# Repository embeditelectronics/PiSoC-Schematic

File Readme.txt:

PiSoC Schematic
----------------

Includes Eagle schematic and board layout for the PiSoC.

Copyright (c) 2015, Embedit Electronics

This work is licensed under a Creative Commons Attribution-ShareAlike 3.0 License. You can view a copy of it here: http://creativecommons.org/licenses/by-sa/3.0/us/

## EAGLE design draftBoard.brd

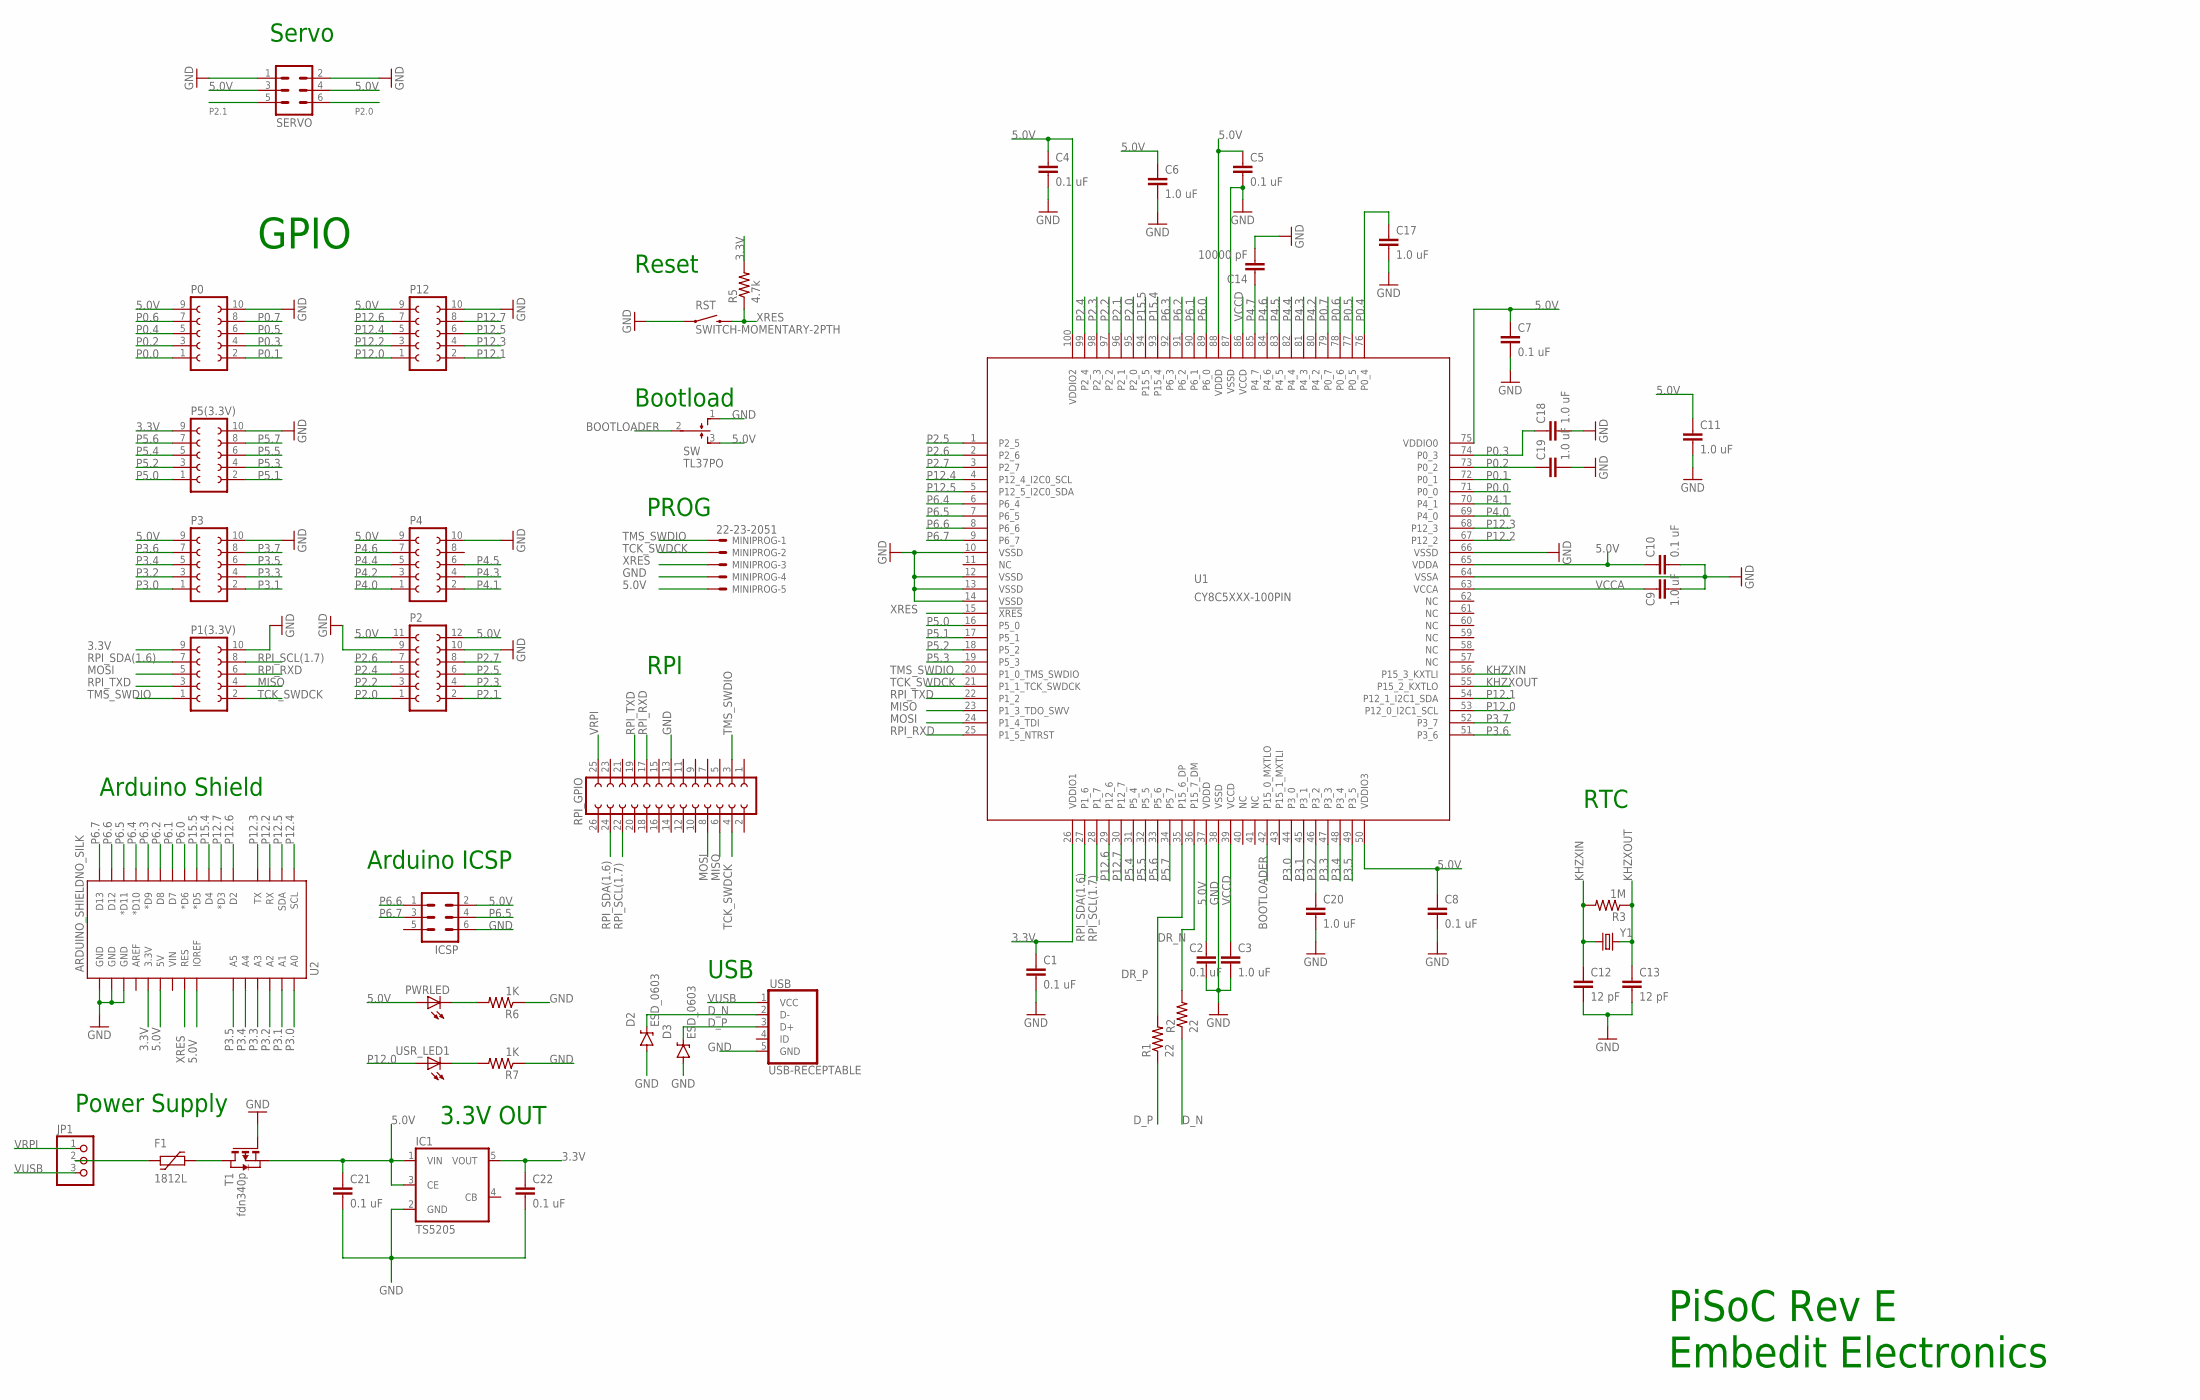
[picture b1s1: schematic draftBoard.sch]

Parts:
C1, C2, C4, C5, C7, C8, C10, C21, C22: 0.1 uF; 0603-CAP@1
C3, C6, C9, C11, C17, C18, C19, C20: 1.0 uF; 0603-CAP@1
C12, C13: 12 pF; 0603-CAP@1
C14: 10000 pF; 0603-CAP@1
D2, D3: ESD_0603; 0603-CAP
F1: 1812L
IC1: TS5205; SOT25
ICSP: MA03-2
JP1: PINHD-1X3; 1X03
MINIPROG: 22-23-2051
P0, P1(3.3V), P3, P4, P5(3.3V), P12: FE05-2
P2: FE06-2
PWRLED: LED0603; LED-0603
R1, R2: 22; 0603-RES
R3: 1M; 0603-RES
R5: 4.7k; 0603-RES
R6, R7: 1K; 0603-RES
RPI_GPIO: FE13-2
RST: SWITCH-MOMENTARY-2PTH; TACTILE-PTH
SERVO: MA03-2
SW: TL37PO; TL3XPO
T1: fdn340p; SOT-23
U1: CY8C5XXX-100PIN; TQFP-14X14-100
U2: ARDUINO_SHIELDNO_SILK; DUEMILANOVE_VIAS
USB: USB-RECEPTABLE; FCI-10103594-0001LF
USR_LED1: LED0603; LED-0603
Y1: CRYSTALTC26H; TC26H

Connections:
3.3V: C1.1, C22.1, IC1.5 (VOUT), P1(3.3V).9, P5(3.3V).9, R5.2, U1.26 (VDDIO1), U2.3.3V
5.0V: C2.1, C4.1, C5.1, C6.1, C7.1, C8.1, C10.1, C11.1, C21.1, IC1.1 (VIN), IC1.3 (CE), ICSP.2, MINIPROG.5, P0.9, P2.11, P2.12, P3.9, P4.9, P12.9, PWRLED.A, SERVO.3, SERVO.4, SW.3 (S), T1.2 (S), U1.37 (VDDD), U1.50 (VDDIO3), U1.65 (VDDA), U1.75 (VDDIO0), U1.88 (VDDD), U1.100 (VDDIO2), U2.5V, U2.IOREF
BOOTLOADER: SW.2, U1.42 (P15_0_MXTLO)
DR_N: R2.2, U1.36 (P15_7_DM)
DR_P: R1.2, U1.35 (P15_6_DP)
D_N: D2.1 (C), R2.1, USB.2 (D-)
D_P: D3.1 (C), R1.1, USB.3 (D+)
GND: C1.2, C2.2, C3.2, C4.2, C5.2, C6.2, C7.2, C8.2, C9.2, C10.2, C11.2, C12.2, C13.2, C14.2, C17.2, C18.2, C19.2, C20.2, C21.2, C22.2, D2.2 (A), D3.2 (A), IC1.2 (GND), ICSP.6, MINIPROG.4, P0.10, P1(3.3V).10, P2.9, P2.10, P3.10, P4.10, P5(3.3V).10, P12.10, R6.1, R7.1, RPI_GPIO.13, RST.1, SERVO.1, SERVO.2, SW.1 (O), T1.3 (G), U1.10 (VSSD), U1.12 (VSSD), U1.13 (VSSD), U1.14 (VSSD), U1.38 (VSSD), U1.64 (VSSA), U1.66 (VSSD), U1.87 (VSSD), U2.GND@0 (GND), U2.GND@1 (GND), U2.GND@2 (GND), USB.5 (GND)
KHZXIN: C12.1, R3.2, U1.56 (P15_3_KXTLI), Y1.1
KHZXOUT: C13.1, R3.1, U1.55 (P15_2_KXTLO), Y1.2
MISO: P1(3.3V).4, RPI_GPIO.6, U1.23 (P1_3_TDO_SWV)
MOSI: P1(3.3V).5, RPI_GPIO.8, U1.24 (P1_4_TDI)
unnamed: PWRLED.C, R6.2
unnamed: F1.P$1 (1), JP1.2
unnamed: F1.P$2 (2), T1.1 (D)
unnamed: R7.2, USR_LED1.C
P0.0: P0.1, U1.71 (P0_0)
P0.1: P0.2, U1.72 (P0_1)
P0.2: C19.1, P0.3, U1.73 (P0_2)
P0.3: C18.1, P0.4, U1.74 (P0_3)
P0.4: C17.1, P0.5, U1.76 (P0_4)
P0.5: P0.6, U1.77 (P0_5)
P0.6: P0.7, U1.78 (P0_6)
P0.7: P0.8, U1.79 (P0_7)
P2.0: P2.1, SERVO.6, U1.95 (P2_0)
P2.1: P2.2, SERVO.5, U1.96 (P2_1)
P2.2: P2.3, U1.97 (P2_2)
P2.3: P2.4, U1.98 (P2_3)
P2.4: P2.5, U1.99 (P2_4)
P2.5: P2.6, U1.1 (P2_5)
P2.6: P2.7, U1.2 (P2_6)
P2.7: P2.8, U1.3 (P2_7)
P3.0: P3.1, U1.44 (P3_0), U2.A0
P3.1: P3.2, U1.45 (P3_1), U2.A1
P3.2: C20.1, P3.3, U1.46 (P3_2), U2.A2
P3.3: P3.4, U1.47 (P3_3), U2.A3
P3.4: P3.5, U1.48 (P3_4), U2.A4
P3.5: P3.6, U1.49 (P3_5), U2.A5
P3.6: P3.7, U1.51 (P3_6)
P3.7: P3.8, U1.52 (P3_7)
P4.0: P4.1, U1.69 (P4_0)
P4.1: P4.2, U1.70 (P4_1)
P4.2: P4.3, U1.80 (P4_2)
P4.3: P4.4, U1.81 (P4_3)
P4.4: P4.5, U1.82 (P4_4)
P4.5: P4.6, U1.83 (P4_5)
P4.6: P4.7, U1.84 (P4_6)
P4.7: C14.1, U1.85 (P4_7)
P5.0: P5(3.3V).1, U1.16 (P5_0)
P5.1: P5(3.3V).2, U1.17 (P5_1)
P5.2: P5(3.3V).3, U1.18 (P5_2)
P5.3: P5(3.3V).4, U1.19 (P5_3)
P5.4: P5(3.3V).5, U1.31 (P5_4)
P5.5: P5(3.3V).6, U1.32 (P5_5)
P5.6: P5(3.3V).7, U1.33 (P5_6)
P5.7: P5(3.3V).8, U1.34 (P5_7)
P6.0: U1.89 (P6_0), U2.D6 (*D6)
P6.1: U1.90 (P6_1), U2.D7
P6.2: U1.91 (P6_2), U2.D8
P6.3: U1.92 (P6_3), U2.D9 (*D9)
P6.4: U1.6 (P6_4), U2.D10 (*D10)
P6.5: ICSP.4, U1.7 (P6_5), U2.D11 (*D11)
P6.6: ICSP.1, U1.8 (P6_6), U2.D12
P6.7: ICSP.3, U1.9 (P6_7), U2.D13
P12.0: P12.1, U1.53 (P12_0_I2C1_SCL), USR_LED1.A
P12.1: P12.2, U1.54 (P12_1_I2C1_SDA)
P12.2: P12.3, U1.67 (P12_2), U2.RX
P12.3: P12.4, U1.68 (P12_3), U2.TX
P12.4: P12.5, U1.4 (P12_4_I2C0_SCL), U2.SCL
P12.5: P12.6, U1.5 (P12_5_I2C0_SDA), U2.SDA
P12.6: P12.7, U1.29 (P12_6), U2.D2
P12.7: P12.8, U1.30 (P12_7), U2.D3 (*D3)
P15.4: U1.93 (P15_4), U2.D4
P15.5: U1.94 (P15_5), U2.D5 (*D5)
RPI_RXD: P1(3.3V).6, RPI_GPIO.17, U1.25 (P1_5_NTRST)
RPI_SCL(1.7): P1(3.3V).8, RPI_GPIO.22, U1.28 (P1_7)
RPI_SDA(1.6): P1(3.3V).7, RPI_GPIO.24, U1.27 (P1_6)
RPI_TXD: P1(3.3V).3, RPI_GPIO.19, U1.22 (P1_2)
TCK_SWDCK: MINIPROG.2, P1(3.3V).2, RPI_GPIO.4, U1.21 (P1_1_TCK_SWDCK)
TMS_SWDIO: MINIPROG.1, P1(3.3V).1, RPI_GPIO.3, U1.20 (P1_0_TMS_SWDIO)
VCCA: C9.1, U1.63 (VCCA)
VCCD: C3.1, U1.39 (VCCD), U1.86 (VCCD)
VRPI: JP1.1, RPI_GPIO.25
VUSB: JP1.3, USB.1 (VCC)
XRES: MINIPROG.3, R5.1, RST.3 (2), U1.15 (!XRES!), U2.RES

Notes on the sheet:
PiSoC Rev E Embedit Electronics
GPIO
PROG
Bootload
Reset
3.3V OUT
RTC
RPI
Arduino Shield
Arduino ICSP
Servo
USB
Power Supply

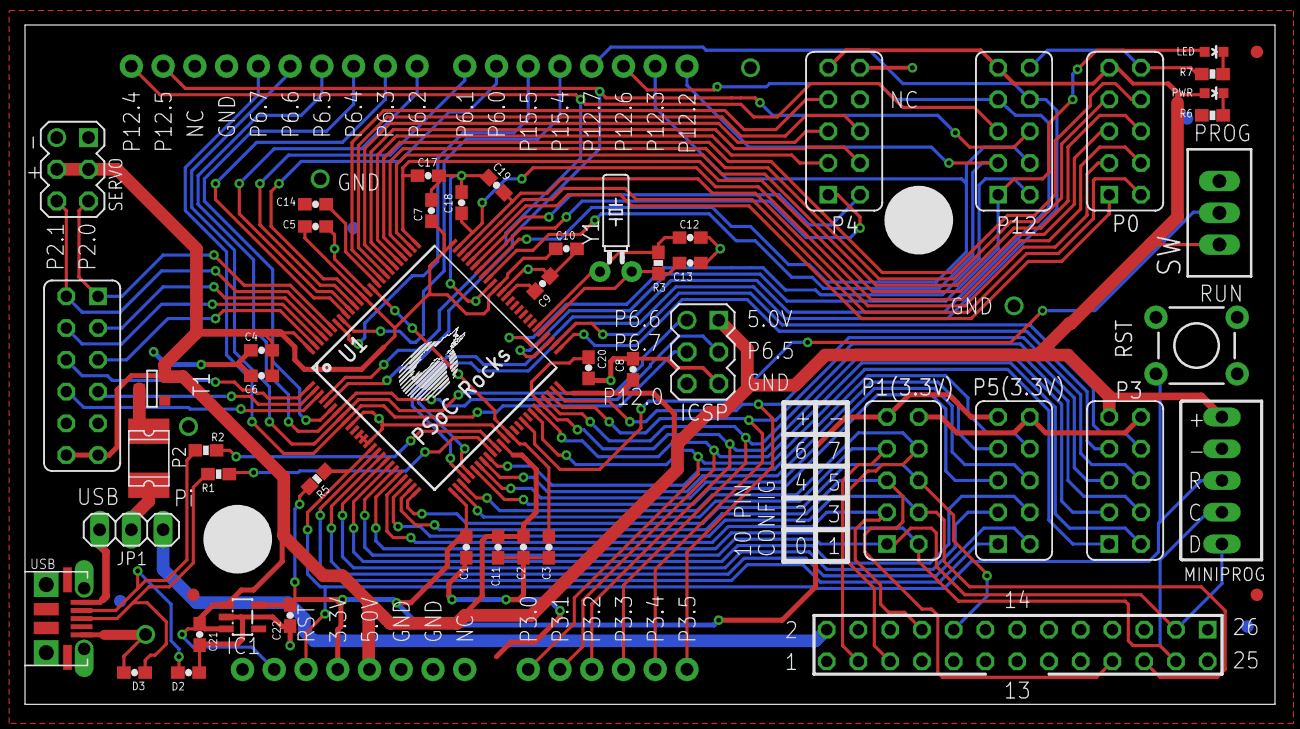
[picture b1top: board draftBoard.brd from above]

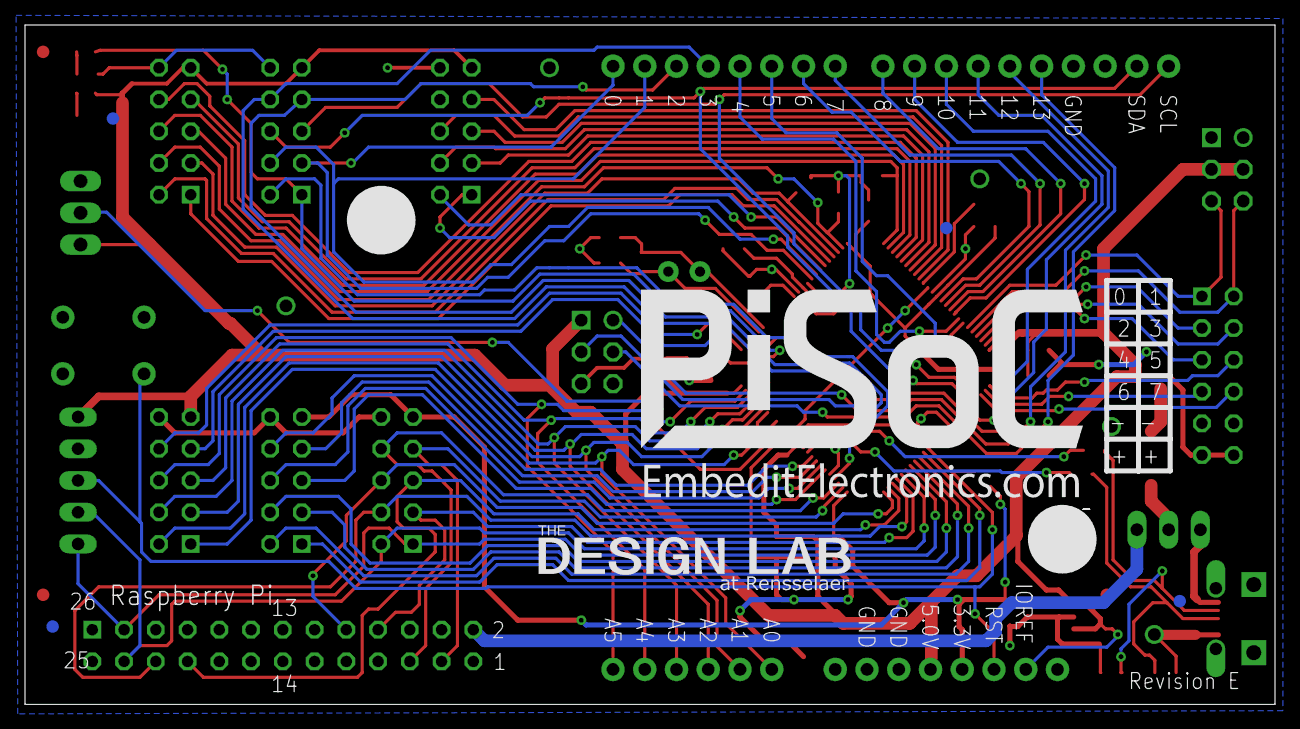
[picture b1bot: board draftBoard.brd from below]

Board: 2 copper layers, 100.0 x 54.3 mm, 62 parts (6 on the bottom side), 85 nets.

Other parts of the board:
U$1: PISOC_LOGO_BOTTOM_MEDIUM
U$2: DESIGN_LAB_LOGO_SMALL
U$3: 12PINPORT
U$4: 10PINPORT
U$6, U$7, U$8, U$9, U$10, U$11, U$12: CIRCLE-1MM-2R

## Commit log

2015-10-21 Added rev E production board. Replaced one pmod header with a servo header. Changed some pin locations including LED and bootloader switch. Added reverse voltage protection.

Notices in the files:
parts and their libraries:
SparkFun-Boards: Licensing: CC v3.0 Share-Alike You are welcome to use this library for commercial purposes.
